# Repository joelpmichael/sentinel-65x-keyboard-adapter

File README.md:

# Sentinel 65X Keyboard Adapter

Nothing to see here yet

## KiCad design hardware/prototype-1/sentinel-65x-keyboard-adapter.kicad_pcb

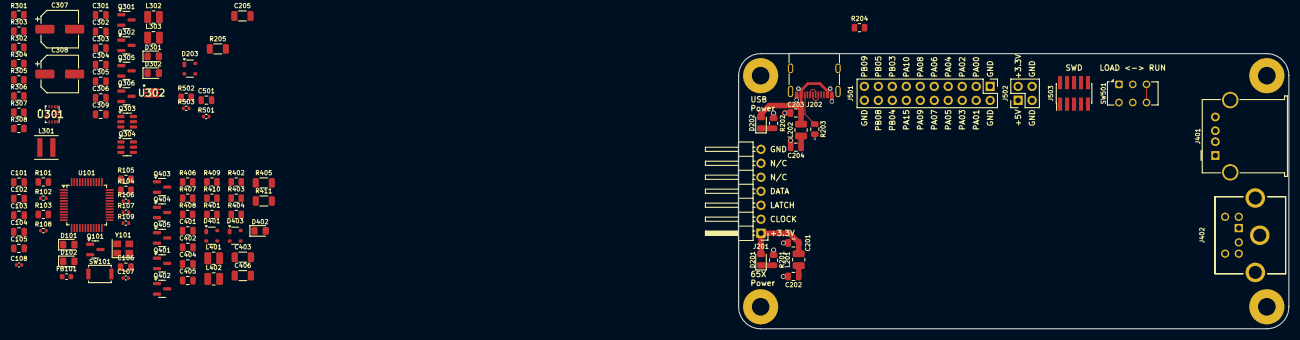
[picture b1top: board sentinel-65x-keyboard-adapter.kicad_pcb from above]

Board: 6 copper layers, 100.0 x 50.0 mm, 108 parts (0 on the bottom side), 67 nets.

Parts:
C101, C102, C103, C104, C105, C106, C201, C203, C301, C303, C306, C401, C404, C501: 0.1u; C_0805_2012Metric
C107, C108: 10p; C_0402_1005Metric
C202, C204, C302, C309, C402, C405: 10u; C_0805_2012Metric
C205, C403, C406: 4.7n; C_1206_3216Metric
C304, C305: 1u; C_0805_2012Metric
C307, C308: 47u; CP_Elec_6.3x5.7
D101, D102, D201, D202, D301, D302, D402: RED; LED_0805_2012Metric_Pad1.15x1.40mm_HandSolder
D203, D401, D403: PRTR5V0U2X; SOT-143
FB101: 220R@100MHz; L_0603_1608Metric
J201: Controller Port; PinHeader_1x07_P2.54mm_Horizontal
J202: USB_C_Receptacle_USB2.0_14P; USB_C_Receptacle_G-Switch_GT-USB-7010ASV
J401: USB_A; USB_A_Molex_67643_Horizontal
J402: Mini-DIN-6; 57492661
J501: Conn_02x10_Odd_Even; PinHeader_2x10_P2.54mm_Vertical
J502: Conn_02x02_Odd_Even; PinHeader_2x02_P2.54mm_Vertical
J503: Conn_ARM_JTAG_SWD_10; PinHeader_2x05_P1.27mm_Vertical_SMD
L201, L202, L302, L303, L401, L402: 2.2u; L_1008_2520Metric
L301: 1.5u; L_Coilcraft_XxL4020
Q101, Q305, Q306, Q401, Q402, Q403: 2N7002K; SOT-23
Q301, Q302, Q404, Q405: FSS2301S; SOT-23
Q303, Q304: DMMT5401; SOT-23-6
R101, R105, R301, R303, R305, R306, R401, R402, R403, R404, R406, R409, R502: 10k; R_0805_2012Metric
R102, R501, R503: 1k; R_0402_1005Metric
R103, R104, R307: 160; R_0805_2012Metric
R106, R107, R108, R109: 10; R_0402_1005Metric
R201, R204, R308, R410: 330; R_0805_2012Metric
R202, R203: 5.1k; R_0805_2012Metric
R205, R405, R411: 1M; R_1206_3216Metric
R302, R304: 47k; R_0805_2012Metric
R407: 2R; R_0805_2012Metric
R408: 1k; R_0805_2012Metric
SW101: SW_Push; SW_Push_SPST_NO_Alps_SKRK
SW501: SW_Slide_DPDT; SW_CK_JS202011CQN_DPDT_Straight
U101: CH32V203C8T6; LQFP-48_7x7mm_P0.5mm
U301: TPS630701RNMR
U302: LP5912-3.3DRVR; SON65P200X200X80-7N
Y101: 8.000MHz; Crystal_SMD_3225-4Pin_3.2x2.5mm

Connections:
+3V3: J502.2, J503.1 (VTref), Q401.1 (G), Q402.1 (G), R402.2, R404.2, R503.1, SW501.6 (C)
+5V: C402.1, D401.4 (VCC), J502.1, L401.2, Q404.2 (S), Q405.2 (S), R401.2, R403.2, R409.2
/+3V3: C101.1, C102.1, C103.1, C104.1, C304.1, D101.2 (A), D102.2 (A), D301.2 (A), FB101.2, R101.2, R105.2, U101.1 (VBAT), U101.24 (VDD_1), U101.36 (VDD_2), U101.48 (VDD_3), U302.1 (OUT)
/+5V: C305.1, C306.1, L303.1, R306.2, U302.6 (IN)
/+5V.65X: C202.2, L201.2, Q301.3 (D), Q303.6 (E1)
/+5V.USB: C204.1, D203.4 (VCC), L202.2, Q101.1 (G), Q302.3 (D), Q304.6 (E1)
/Data Inputs/PS2.+5V: C405.1, D402.2 (A), D403.4 (VCC), J402.4, L402.1
/Data Inputs/PS2.CLOCK: Q401.2 (S), R402.1
/Data Inputs/PS2.CLOCK_5V: D403.3 (I/O2), J402.5, Q401.3 (D), R401.1
/Data Inputs/PS2.DATA: Q402.2 (S), R404.1
/Data Inputs/PS2.DATA_5V: D403.2 (I/O1), J402.1, Q402.3 (D), R403.1
/Data Inputs/PS2.POWER: Q403.1 (G), Q404.1 (G), R406.2
/Data Inputs/USB1.DM: D401.2 (I/O1), J401.2 (D-)
/Data Inputs/USB1.DP: D401.3 (I/O2), J401.3 (D+)
/EXT_PWR: Q101.3 (D), R105.1, U101.28 (PB15)
/Hacking/BOOT0: C501.1, R502.1
/Hacking/SWCLK: J503.4 (SWCLK/TCK), R503.2
/LED_STATUS: R104.1, U101.2 (PC13)
/LED_SYSTEM: R103.1, U101.3 (PC14/OSC32_IN)
/NRST: C106.1, Q305.1 (G), R101.1, R102.2, U101.7 (NRST), U302.3 (PG)
/OSC_IN: C107.2, U101.5 (OSC_IN/PD0), Y101.3
/OSC_OUT: C108.2, U101.6 (OSC_OUT/PD1), Y101.1
/PB6/USB2_DM: R106.1, U101.42 (PB6/USB2_DM)
/PB7/USB2_DP: R107.2, U101.43 (PB7/USB2_DP)
/Power Supply/+5V_U: C307.1, C308.1, C309.1, D302.2 (A), L303.2, U301.5 (FB), U301.7 (VOUT_1), U301.8 (VOUT_2)
/Power Supply/PG_5V: Q306.1 (G), R306.1, U301.2 (PG), U302.4 (EN)
/SNES.CLOCK: J201.2, U101.18 (PB0)
/SNES.DATA: J201.4, U101.20 (PB2/BOOT1)
/SNES.LATCH: J201.3, U101.19 (PB1)
/USB1_DM/PA11: R109.2, U101.32 (USB1_DM/PA11)
/USB1_DP/PA12: R108.1, U101.33 (USB1_DP/PA12)
/USB2.DM: D203.3 (I/O2), J202.A7 (D-), J202.B7 (D-), R106.2
/USB2.DP: D203.2 (I/O1), J202.A6 (D+), J202.B6 (D+), R107.1
/VDDA: C105.1, FB101.1, U101.9 (VDDA)
GND: C101.2, C102.2, C103.2, C104.2, C105.2, C106.2, C107.1, C108.1, C201.1, C202.1, C203.2, C204.2, C205.2, C301.2, C302.2, C303.2, C304.2, C305.2, C306.2, C307.2, C308.2, C309.2, C401.2, C402.2, C403.2, C404.2, C405.2, C406.2, C501.2, J201.7, J202.A1 (GND), J202.A12 (GND), J202.B1 (GND), J202.B12 (GND), J401.4 (GND), J402.3, J501.1, J501.2, J501.20, J502.3, J502.4, J503.3 (GND), J503.5 (GND), J503.9 (GNDDetect), Q101.2 (S), Q305.2 (S), Q306.2 (S), Q403.2 (S), R201.1, R202.1, R203.1, R204.1, R205.2, R301.1, R302.1, R303.1, R304.1, R405.2, R406.1, R410.1, R411.2, R501.1, SW101.1, SW501.4 (A), U101.4 (PC15/OSC32_OUT), U101.8 (VSSA), U101.23 (VSS_1), U101.35 (VSS_2), U101.47 (VSS_3), U301.4 (GND), U301.6 (FB2), U301.10 (PGND), U301.15 (VSEL), U302.5 (GND), U302.7 (EP), Y101.2, Y101.4
GNDS: C205.1, C403.1, C406.1, D203.1 (GND), D401.1 (GND), D403.1 (GND), J202.S1 (SHIELD), J401.5 (Shield), R205.1, R405.1, R411.1
unnamed: D101.1 (K), R103.2
unnamed: D102.1 (K), R104.2
unnamed: C201.2, D201.2 (A), J201.1, L201.1
unnamed: D201.1 (K), R201.2
unnamed: C203.1, D202.2 (A), J202.A4 (VBUS), J202.A9 (VBUS), J202.B4 (VBUS), J202.B9 (VBUS), L202.1
unnamed: D202.1 (K), R204.2
unnamed: D301.1 (K), R307.2
unnamed: D302.1 (K), R308.2
unnamed: D402.1 (K), R410.2
unnamed: J202.A5 (CC1), R203.2
unnamed: J202.B5 (CC2), R202.2
unnamed: C401.1, J401.1 (VBUS), L401.1
unnamed: Q301.1 (G), Q303.4 (C2), R302.2
unnamed: Q302.1 (G), Q304.4 (C2), R304.2
unnamed: Q303.1 (C1), Q303.2 (B1), Q303.3 (B2), R301.2
unnamed: Q304.1 (C1), Q304.2 (B1), Q304.3 (B2), R303.2
unnamed: Q305.3 (D), R307.1
unnamed: Q306.3 (D), R308.1
unnamed: Q403.3 (D), R407.1
unnamed: Q404.3 (D), R408.1
unnamed: C404.1, L402.2, Q405.3 (D)
unnamed: Q405.1 (G), R407.2, R408.2, R409.1
unnamed: R102.1, SW101.2
unnamed: R501.2, SW501.2 (B)
unnamed: R502.2, SW501.5 (B)
unnamed: R305.2, U301.1 (PS/S), U301.14 (EN)
unnamed: L301.2, U301.11 (L1)
unnamed: L301.1, U301.9 (L2)
unnamed: C301.1, U301.3 (VAUX)
VBUS: C303.1, L302.2, Q301.2 (S), Q302.2 (S), Q303.5 (E2), Q304.5 (E2)
VBUS_U: C302.1, L302.1, R305.1, U301.12 (VIN_1), U301.13 (VIN_2)

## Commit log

2024-06-17 git better
2024-06-17 git more fixed
2024-06-17 MacOS was (not) here
2024-06-17 Initial content
2024-06-18 initial rusty bits
2024-06-18 C bits
2024-06-18 add riscv32imac target because i keep forgetting it; pin rust nightly to 2024-06-12 because of https://github.com/embassy-rs/embassy/issues/3078
2024-06-18 required settings for rust-analyzer
2024-06-20 completed keyboard protocol
2024-06-21 Split controller port specification to its own document; minor updates
2024-06-27 SNES controller port data line logic level appears to be inverted from the bit value
2024-07-03 Controller port and keyboard adapter protocol fixes
2024-07-03 another TODO item
2024-07-07 add make files
2024-07-07 fucking vendor SDK's
2024-07-07 that... seems to be ok now?
2024-07-10 system init function skeletons; system init for sentinel_65x_controller function
2024-07-10 important note about Sentinel 65X Prototype 4.0 having different voltage on SNES ports than prototype 4.1 and later
2024-07-11 screwing with build dirs
2024-07-11 more shenanigans
2024-07-12 just more shenanigans, there might even be useful code soon?
2024-07-12 more shenanigans, just like a bought one
2024-07-12 more yak shaving
2024-07-12 it's a queue!
2024-07-13 struct and union crimes
2024-07-15 teach ld about .ramfunc and .slowfunc
2024-07-15 holy shit i can't believe this works
2024-07-15 "\t" -> " "
2024-07-16 the CH32V203 is a lying liar that lies
2024-07-16 make flash
2024-07-16 make flash goes here
2024-07-16 make release
2024-07-16 EBREAK in debug builds
2024-07-17 starting to look like a keyboard now!
2024-07-18 keyboard now does auto-repeat!
2024-07-18 that's a lot of code for a keyboard...
2024-07-24 C formatter goes brblblblblbl
2024-07-24 formatter go ebebebebebebe
2024-08-07 HOLY SHIT IT RECEIVED THE FIRST SETUP FRAME!!!
2024-08-09 This seems to RX the setup frame pretty reliably now! Time to start speaking when spoken to...
2024-08-13 WHY DID NOBODY TELL ME ABOUT THE TinyUSB PROJECT!
2024-08-14 prep for TinyUSB
2025-04-03 KiCad Excludes
2025-04-03 fresh schematic bits
2025-05-14 pull in TinyUSB stack, upgrade to MRS 2, maybe this yak is finally shaved?
2025-05-14 hardware updates
2025-05-14 more git excludes
